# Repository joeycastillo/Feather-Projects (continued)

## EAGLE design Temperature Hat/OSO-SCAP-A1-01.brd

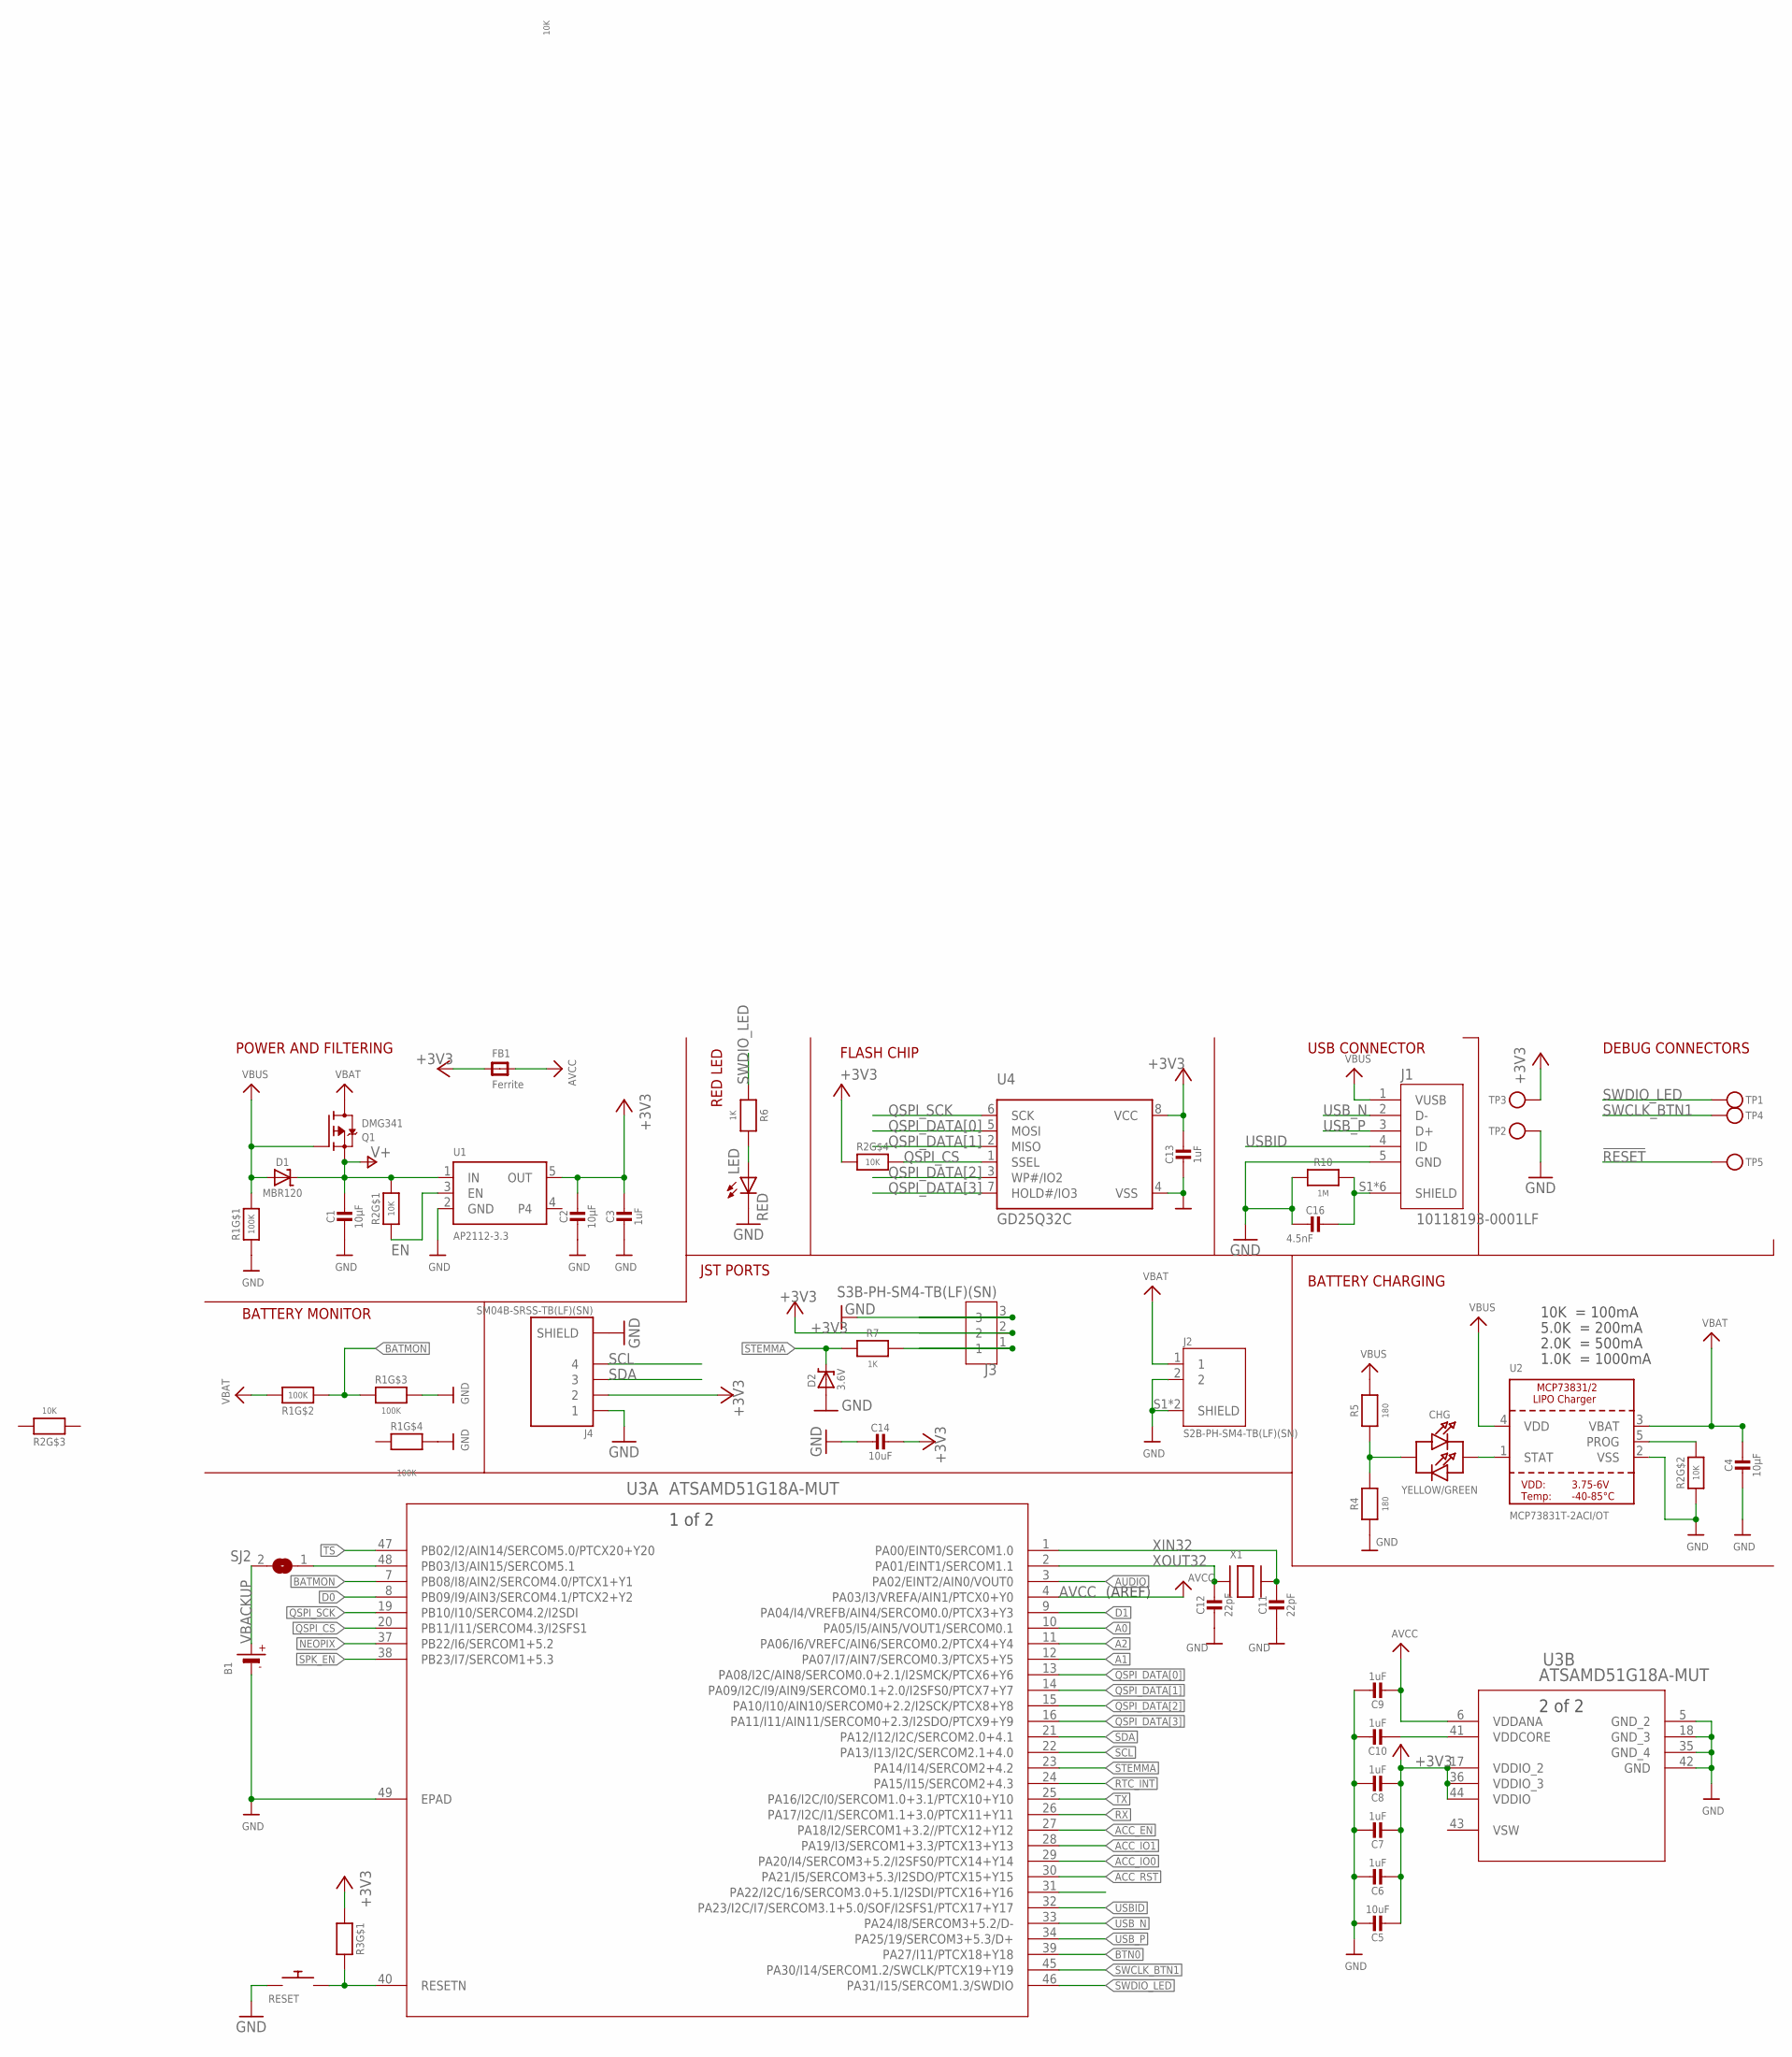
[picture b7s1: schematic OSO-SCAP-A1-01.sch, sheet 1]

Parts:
B1: CR1220; CR1220-2
C1, C2, C4: 10µF; 0805-NO
C3, C6, C7, C8, C13: 1uF; 0805-NO
C5: 10uF; 0805_10MGAP
C9, C10: 1uF; 0805_10MGAP
C11, C12: 22pF; 0805-NO
C14: 10uF; 0805-NO
C16: 4.5nF; 0805-NO
CHG: YELLOW/GREEN; CHIPLED_1206
D1: MBR120; SOD-123
D2: 3.6V; SOD-123
FB1: Ferrite; _0805MP
J1: 10118193-0001LF; FCI_10118193-0001LF
J2: S2B-PH-SM4-TB(LF)(SN); JST_S2B-PH-SM4-TB(LF)(SN)
J3: S3B-PH-SM4-TB(LF)(SN); JST_S3B-PH-SM4-TB(LF)(SN)
J4: SM04B-SRSS-TB(LF)(SN); JST_SM04B-SRSS-TB(LF)(SN)
LED: RED; CHIPLED_1206
Q1: DMG341; SOT23-R
R1: 100K; EXBV8V
R2, R3: 10K; EXBV8V
R4, R5: 180; 0805-NO
R6, R7: 1K; 0805-NO
R10: 1M; 0805-NO
RESET: SWITCH_PUSHBUTTONC&K_KSS; BTN_CK_KSS
SJ2: SOLDERJUMPERREFLOW_NOPASTE; SOLDERJUMPER_REFLOW_NOPASTE
TP1, TP2, TP3, TP4, TP5: TESTPOINTROUND1.5MMNO; TESTPOINT_ROUND_1.5MM_NO
U1: AP2112-3.3; SOT23-5
U2: MCP73831T-2ACI/OT; SOT23-5
U3: ATSAMD51G18A-MUT; QFN48_7X7MC
U4: GD25Q32C; MICROBUILDER_SOIC8_150MIL
X1: XTAL-3.2X1.5; XTAL3215

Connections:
!RESET: R3.8 (2), RESET.P$2, TP5.P$1, U3.40 (RESETN)
+3V3: C2.1, C3.1, C5.2, C6.2, C7.2, C8.2, C13.1, C14.1, FB1.1, J3.2, J4.2, R2.4 (1), R3.1, TP3.P$1, U1.5 (OUT), U3.17 (VDDIO_2), U3.36 (VDDIO_3), U3.44 (VDDIO), U4.8 (VCC); also elsewhere on the board
A0: U3.10 (PA05/I5/AIN5/VOUT1/SERCOM0.1); also elsewhere on the board
A1: U3.12 (PA07/I7/AIN7/SERCOM0.3/PTCX5+Y5); also elsewhere on the board
A2: U3.11 (PA06/I6/VREFC/AIN6/SERCOM0.2/PTCX4+Y4); also elsewhere on the board
ACC_EN: U3.27 (PA18/I2/SERCOM1+3.2//PTCX12+Y12); also elsewhere on the board
ACC_IO0: U3.29 (PA20/I4/SERCOM3+5.2/I2SFS0/PTCX14+Y14); also elsewhere on the board
ACC_IO1: U3.28 (PA19/I3/SERCOM1+3.3/PTCX13+Y13); also elsewhere on the board
ACC_RST: U3.30 (PA21/I5/SERCOM3+5.3/I2SDO/PTCX15+Y15); also elsewhere on the board
AUDIO: U3.3 (PA02/EINT2/AIN0/VOUT0); also elsewhere on the board
AVCC: C9.2, FB1.2, U3.4 (PA03/I3/VREFA/AIN1/PTCX0+Y0), U3.6 (VDDANA); also elsewhere on the board
BATMON: R1.2 (1), R1.3 (1), U3.7 (PB08/I8/AIN2/SERCOM4.0/PTCX1+Y1)
BTN0: U3.39 (PA27/I11/PTCX18+Y18); also elsewhere on the board
D0: U3.8 (PB09/I9/AIN3/SERCOM4.1/PTCX2+Y2); also elsewhere on the board
D1: U3.9 (PA04/I4/VREFB/AIN4/SERCOM0.0/PTCX3+Y3); also elsewhere on the board
EN: R2.1, U1.3 (EN); also elsewhere on the board
GND: B1.-, C1.2, C2.2, C3.2, C4.2, C5.1, C6.1, C7.1, C8.1, C9.1, C10.1, C11.2, C12.2, C13.2, C14.2, C16.2, D2.A, J1.5 (GND), J2.2, J2.S1 (SHIELD), J2.S2 (SHIELD), J3.3, J4.1, J4.S1 (SHIELD), J4.S2 (SHIELD), LED.C, R1.1, R1.5 (2), R1.6 (2), R2.2 (1), R4.1, R10.2, RESET.P$1, TP2.P$1, U1.2 (GND), U2.2 (VSS), U3.5 (GND_2), U3.18 (GND_3), U3.35 (GND_4), U3.42 (GND), U3.49 (EPAD), U4.4 (VSS); also elsewhere on the board
unnamed: CHG.A, R4.2, R5.1
unnamed: LED.A, R6.2
NEOPIX: U3.37 (PB22/I6/SERCOM1+5.2); also elsewhere on the board
PROG: R2.7 (2), U2.5 (PROG)
QSPI_CS: R2.5 (2), U3.20 (PB11/I11/SERCOM4.3/I2SFS1), U4.1 (SSEL)
QSPI_DATA[0]: U3.13 (PA08/I2C/AIN8/SERCOM0.0+2.1/I2SMCK/PTCX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), U4.5 (MOSI)
QSPI_DATA[1]: U3.14 (PA09/I2C/I9/AIN9/SERCOM0.1+2.0/I2SFS0/P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), U4.2 (MISO)
QSPI_DATA[2]: U3.15 (PA10/I10/AIN10/SERCOM0+2.2/I2SCK/PTCX8+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), U4.3 (WP#/IO2)
QSPI_DATA[3]: U3.16 (PA11/I11/AIN11/SERCOM0+2.3/I2SDO/PTCX9+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), U4.7 (HOLD#/IO3)
QSPI_SCK: U3.19 (PB10/I10/SERCOM4.2/I2SDI), U4.6 (SCK)
RTC_INT: U3.24 (PA15/I15/SERCOM2+4.3); also elsewhere on the board
RX: U3.26 (PA17/I2C/I1/SERCOM1.1+3.0/PTCX11+Y11); also elsewhere on the board
SCL: J4.4, U3.22 (PA13/I13/I2C/SERCOM2.1+4.0); also elsewhere on the board
SDA: J4.3, U3.21 (PA12/I12/I2C/SERCOM2.0+4.1); also elsewhere on the board
SHIELD: C16.1, J1.S1 (SHIELD), J1.S2 (SHIELD), J1.S3 (SHIELD), J1.S4 (SHIELD), J1.S5 (SHIELD), J1.S6 (SHIELD), R10.1
SPK_EN: U3.38 (PB23/I7/SERCOM1+5.3); also elsewhere on the board
STAT: CHG.C, U2.1 (STAT)
STEMMA: D2.C, R7.2, U3.23 (PA14/I14/SERCOM2+4.2)
SWCLK_BTN1: TP4.P$1, U3.45 (PA30/I14/SERCOM1.2/SWCLK/PTCX19+Y19); also elsewhere on the board
SWDIO_LED: R6.1, TP1.P$1, U3.46 (PA31/I15/SERCOM1.3/SWDIO)
TS: U3.47 (PB02/I2/AIN14/SERCOM5.0/PTCX20+Y20); also elsewhere on the board
TX: U3.25 (PA16/I2C/I0/SERCOM1.0+3.1/PTCX10+Y10); also elsewhere on the board
USBID: J1.4 (ID), U3.32 (PA23/I2C/I7/SERCOM3.1+5.0/SOF/I2SFS1/PT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)
USB_N: J1.2 (D-), U3.33 (PA24/I8/SERCOM3+5.2/D-)
USB_P: J1.3 (D+), U3.34 (PA25/19/SERCOM3+5.3/D+)
V+: C1.1, D1.C, Q1.2 (S), R2.8 (2), U1.1 (IN)
VBACKUP: B1.+, SJ2.2; also elsewhere on the board
VBAT: C4.1, J2.1, Q1.3 (D), R1.7 (2), U2.3 (VBAT)
VBUS: D1.A, J1.1 (VUSB), Q1.1 (G), R1.8 (2), R5.2, U2.4 (VDD)
VDDCORE: C10.2, U3.41 (VDDCORE)
VSW: U3.43 (VSW)
XIN32: C11.1, U3.1 (PA00/EINT0/SERCOM1.0), X1.P$2
XOUT32: C12.1, U3.2 (PA01/EINT1/SERCOM1.1), X1.P$1
_STEMMA: J3.1, R7.1
_VBACKUP: SJ2.1, U3.48 (PB03/I3/AIN15/SERCOM5.1)

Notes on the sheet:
POWER AND FILTERING
10K = 100mA
5.0K = 200mA
2.0K = 500mA
1.0K = 1000mA
BATTERY CHARGING
DEBUG CONNECTORS
USB CONNECTOR
BATTERY MONITOR
FLASH CHIP
RED LED
JST PORTS
(AREF)

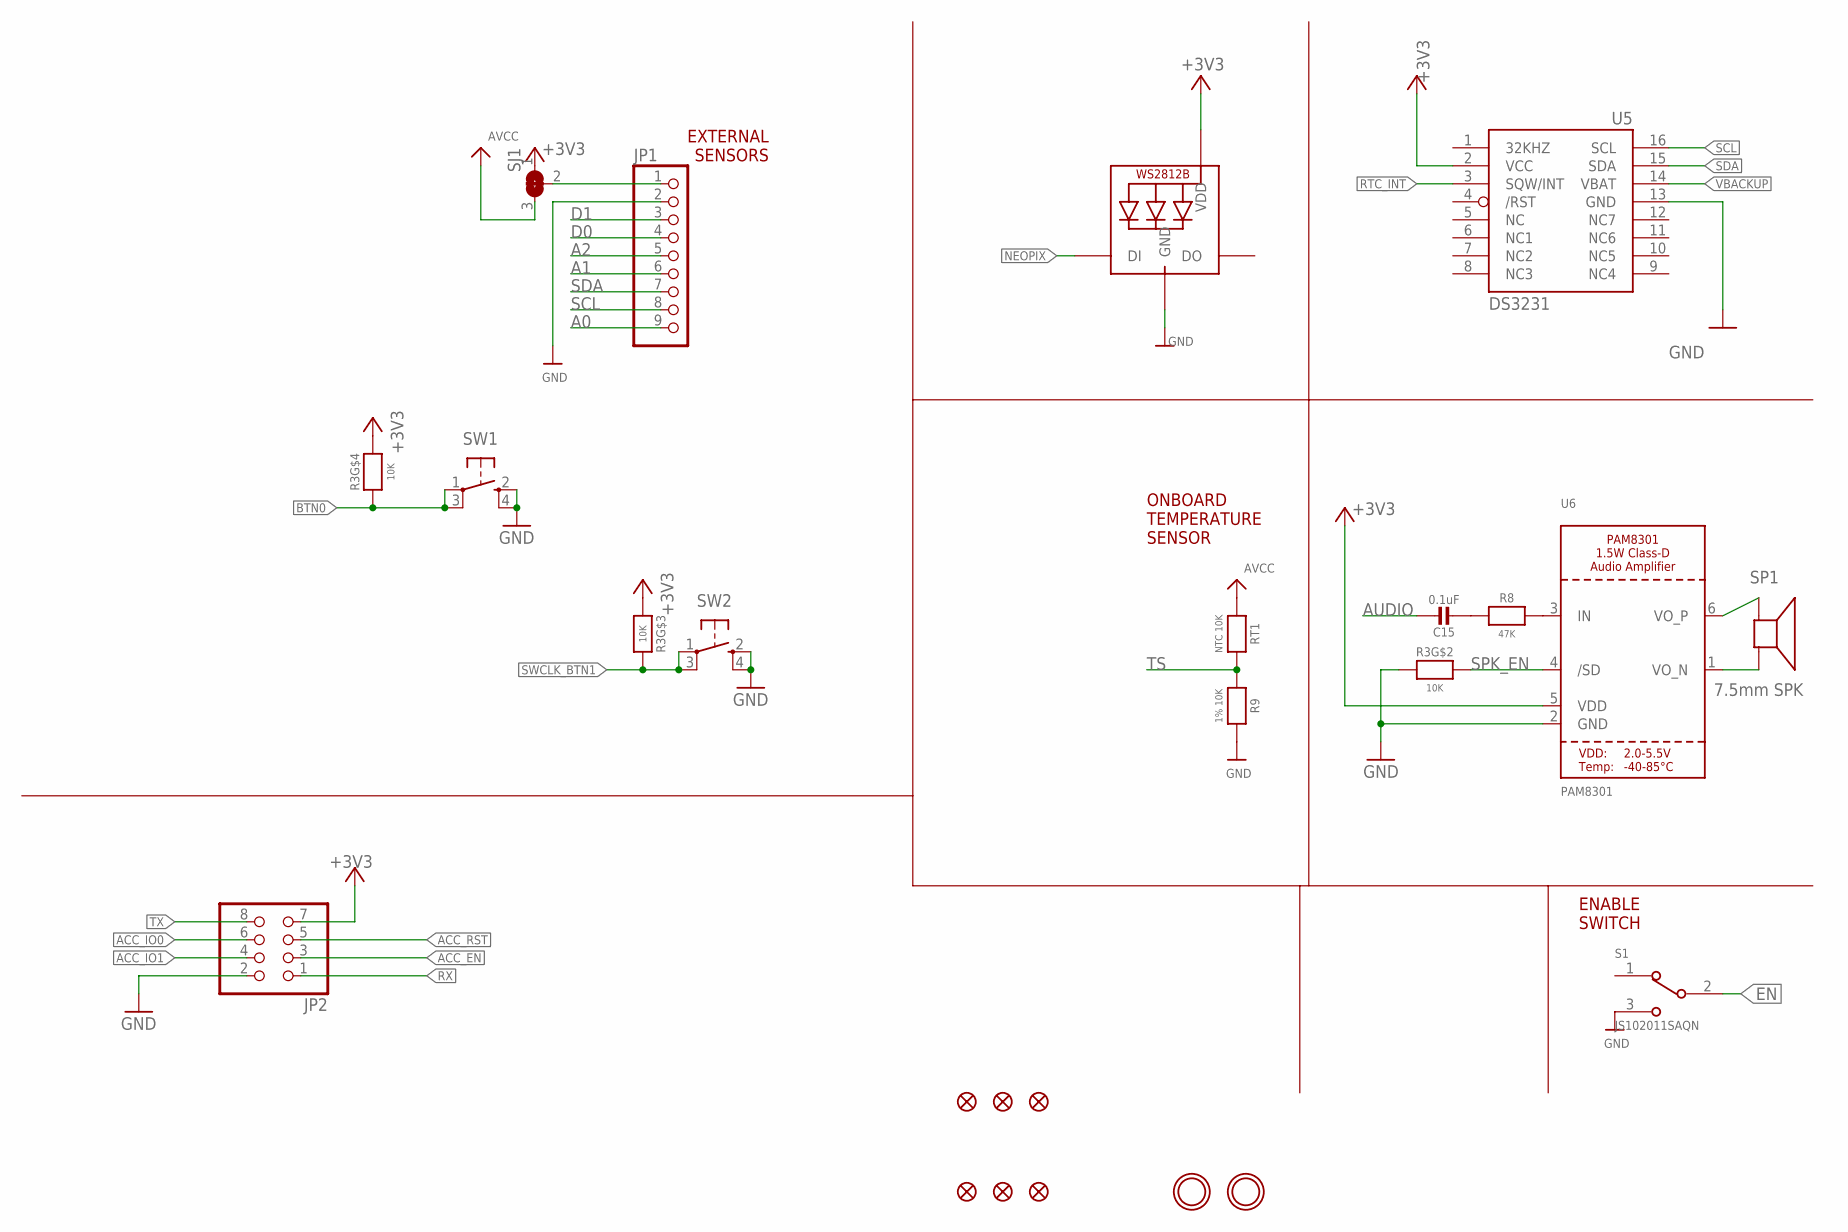
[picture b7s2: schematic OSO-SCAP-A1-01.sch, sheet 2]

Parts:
C15: 0.1uF; 0805-NO
FID1, FID2, FID3, FID4, FID5, FID6: FIDUCIAL_1MM
JP1: HEADER-1X9_JSTSH; JST_SH9
JP2: PINHD-2X4SMT; PINHD_2X4_SMT
NEOPIX: WS2812B_4020
R3: 10K; EXBV8V
R8: 47K; 0805-NO
R9: 1% 10K; 0805-NO
RT1: NTC 10K; 0805-NO
S1: JS102011SAQN; SW_JS102011SAQN
SJ1: SOLDERJUMPER_2WAY; SOLDERJUMPER_2WAY_OPEN_NOPASTE
SP1: 7.5mm SPK; BUZZER_SMT_5MM
SW1, SW2: SPST_TACT-KMR2; KMR2
U5: DS3231/SO; SO16W
U6: PAM8301; SOT23-6
U$1, U$4: MOUNTINGHOLE2.5; MOUNTINGHOLE_2.5_PLATED

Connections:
+3V3: JP2.7, NEOPIX.2 (VDD), R3.3 (1), R3.5 (2), SJ1.1, U5.2 (VCC), U6.5 (VDD); also elsewhere on the board
A0: JP1.9; also elsewhere on the board
A1: JP1.6; also elsewhere on the board
A2: JP1.5; also elsewhere on the board
ACC_EN: JP2.3; also elsewhere on the board
ACC_IO0: JP2.6; also elsewhere on the board
ACC_IO1: JP2.4; also elsewhere on the board
ACC_RST: JP2.5; also elsewhere on the board
AUDIO: C15.1; also elsewhere on the board
AVCC: RT1.1, SJ1.3; also elsewhere on the board
BTN0: R3.4 (1), SW1.1, SW1.3 (P1); also elsewhere on the board
D0: JP1.4; also elsewhere on the board
D1: JP1.3; also elsewhere on the board
EN: S1.2; also elsewhere on the board
GND: JP1.2, JP2.2, NEOPIX.4 (GND), R3.2 (1), R9.2, S1.3, SW1.2 (S), SW1.4 (S1), SW2.2 (S), SW2.4 (S1), U5.13 (GND), U6.2 (GND); also elsewhere on the board
unnamed: C15.2, R8.1
unnamed: R8.2, U6.3 (IN)
NEOPIX: NEOPIX.1 (DI); also elsewhere on the board
POWER_OUT: JP1.1, SJ1.2
RTC_INT: U5.3 (SQW/INT); also elsewhere on the board
RX: JP2.1; also elsewhere on the board
SCL: JP1.8, U5.16 (SCL); also elsewhere on the board
SDA: JP1.7, U5.15 (SDA); also elsewhere on the board
SPK_EN: R3.7 (2), U6.4 (/SD); also elsewhere on the board
SPK_N: SP1.+, U6.1 (VO_N)
SPK_P: SP1.-, U6.6 (VO_P)
SWCLK_BTN1: R3.6 (2), SW2.1, SW2.3 (P1); also elsewhere on the board
TS: R9.1, RT1.2; also elsewhere on the board
TX: JP2.8; also elsewhere on the board
VBACKUP: U5.14 (VBAT); also elsewhere on the board

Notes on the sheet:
ENABLE SWITCH
EXTERNAL SENSORS
ONBOARD TEMPERATURE SENSOR

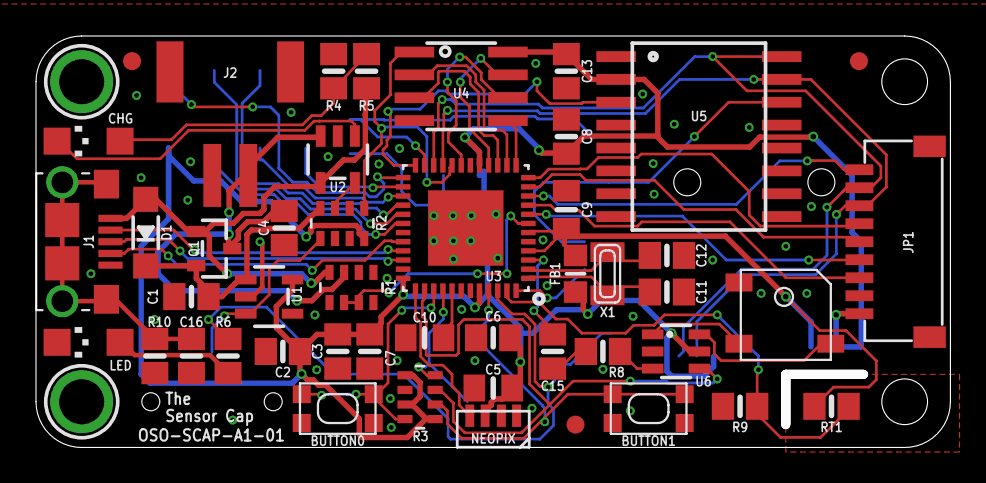
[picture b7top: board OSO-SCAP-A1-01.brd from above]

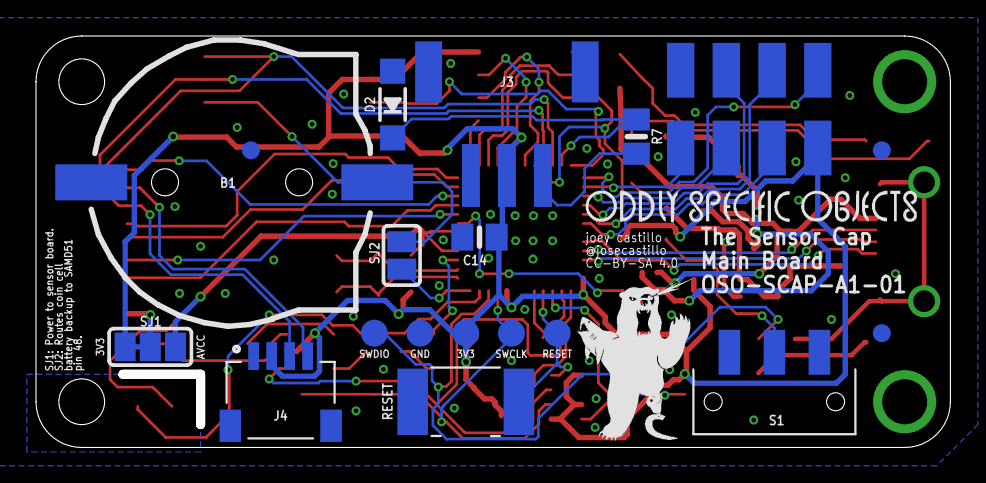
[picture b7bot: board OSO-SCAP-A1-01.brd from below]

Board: 2 copper layers, 50.8 x 22.9 mm, 70 parts (21 on the bottom side), 56 nets.

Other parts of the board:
U$31: OSO_WORDMARK_ONELINE_725MIL_1000DPI
U$32: OSO_BEAR_250X360MIL_1000DPI
